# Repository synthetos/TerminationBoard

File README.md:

# TerminationBoard
Connector termination board for motorized winches

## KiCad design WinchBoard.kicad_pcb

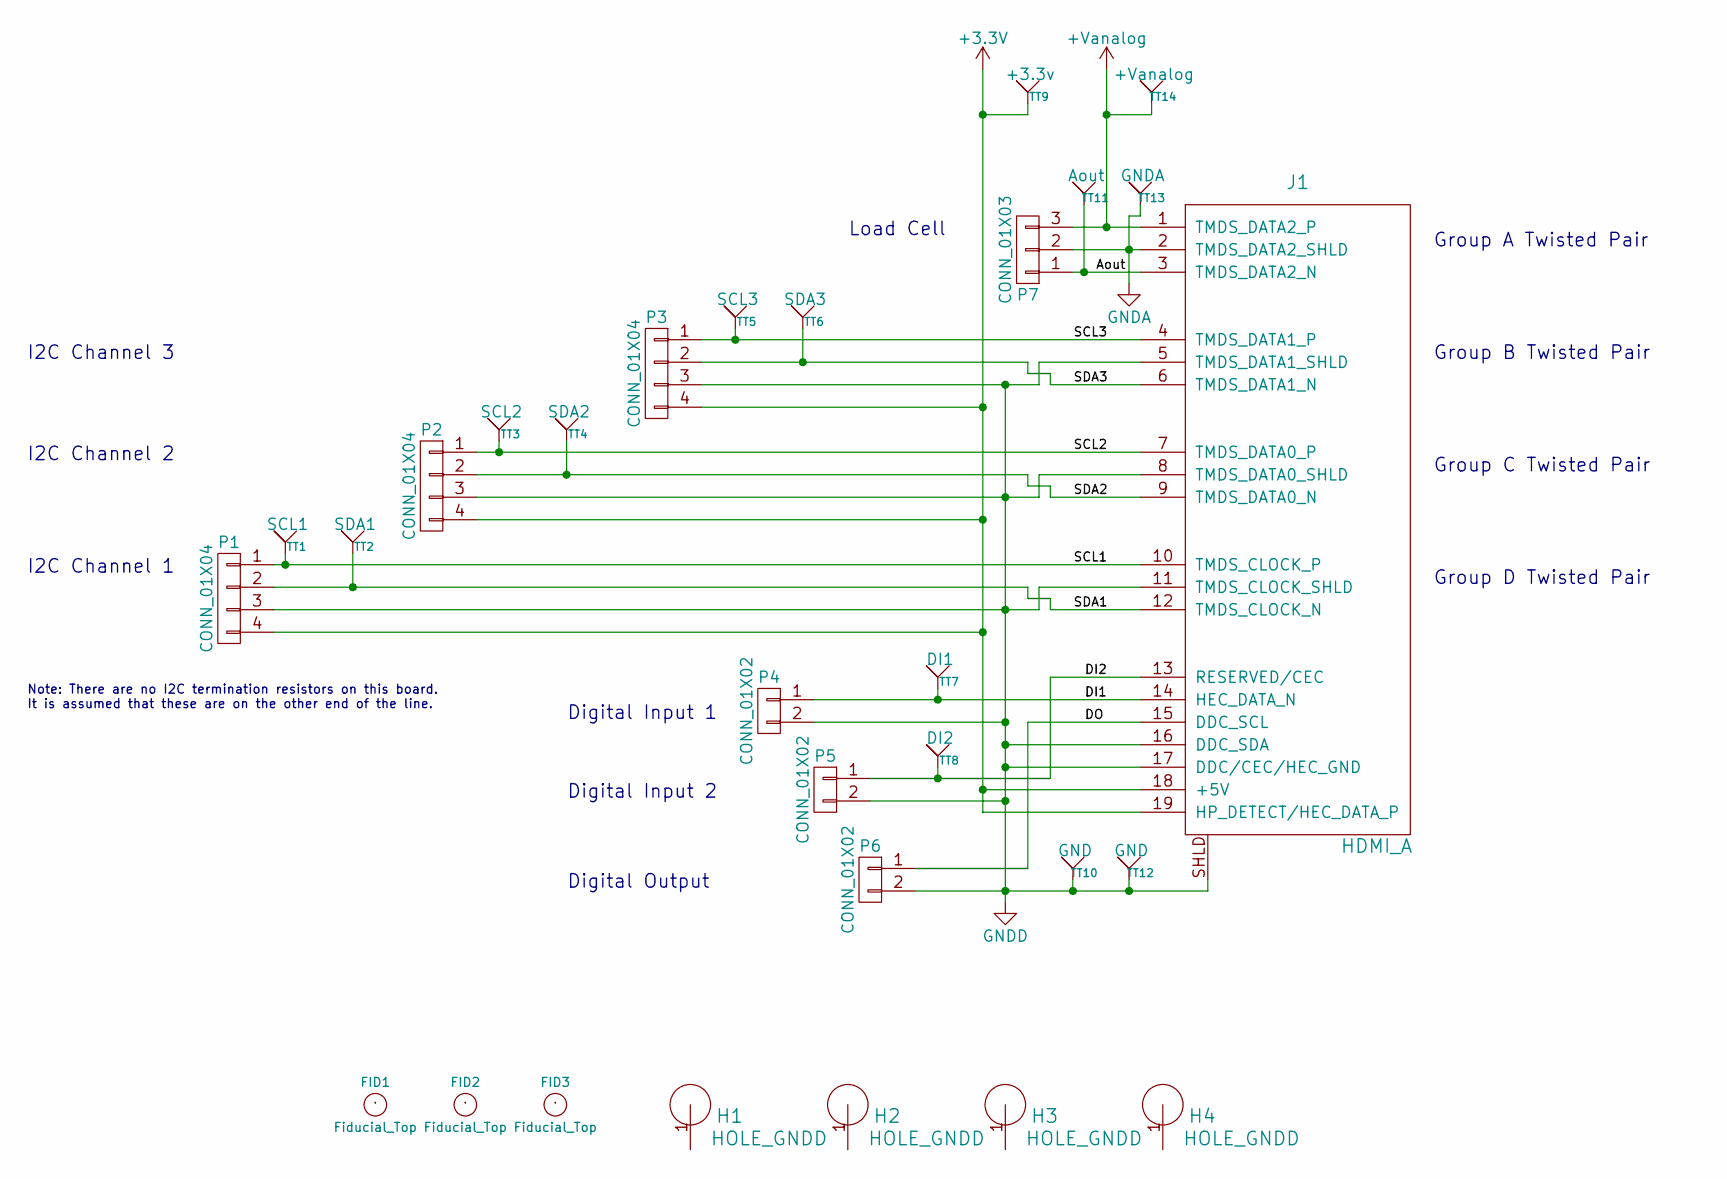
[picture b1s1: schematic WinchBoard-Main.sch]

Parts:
FID1, FID2, FID3: Fiducial_Top; Fiducial_0.040_Top
H1, H2, H3, H4: HOLE_GNDD; MountingHole_3.2mm_M3
J1: HDMI_A; FCI_10029449-11[13]RLF
P1, P2, P3: CONN_01X04; Molex_KK-6410-04_04x2.54mm_Straight
P4, P5, P6: CONN_01X02; Molex_KK-6410-02_02x2.54mm_Straight
P7: CONN_01X03; 0.100_1x3_small
TT1: SCL1; Test_Point_SMD_0.040_Bottom
TT2: SDA1; Test_Point_SMD_0.040_Bottom
TT3: SCL2; Test_Point_SMD_0.040_Bottom
TT4: SDA2; Test_Point_SMD_0.040_Bottom
TT5: SCL3; Test_Point_SMD_0.040_Bottom
TT6: SDA3; Test_Point_SMD_0.040_Bottom
TT7: DI1; Test_Point_SMD_0.040_Bottom
TT8: DI2; Test_Point_SMD_0.040_Bottom
TT9: +3.3v; Test_Point_SMD_0.040_Bottom
TT10, TT12: GND; Test_Point_SMD_0.040_Bottom
TT11: Aout; Test_Point_SMD_0.040_Bottom
TT13: GNDA; Test_Point_SMD_0.040_Bottom
TT14: +Vanalog; Test_Point_SMD_0.040_Bottom

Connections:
+3V3: J1.18 (+5V), J1.19 (HP_DETECT/HEC_DATA_P), P1.4, P2.4, P3.4, TT9.1
+Vanalog: J1.1 (TMDS_DATA2_P), P7.3, TT14.1
/Main/Aout: J1.3 (TMDS_DATA2_N), P7.1, TT11.1
/Main/DI1: J1.14 (HEC_DATA_N), P4.1, TT7.1
/Main/DI2: J1.13 (RESERVED/CEC), P5.1, TT8.1
/Main/DO: J1.15 (DDC_SCL), P6.1
/Main/SCL1: J1.10 (TMDS_CLOCK_P), P1.1, TT1.1
/Main/SCL2: J1.7 (TMDS_DATA0_P), P2.1, TT3.1
/Main/SCL3: J1.4 (TMDS_DATA1_P), P3.1, TT5.1
/Main/SDA1: J1.12 (TMDS_CLOCK_N), P1.2, TT2.1
/Main/SDA2: J1.9 (TMDS_DATA0_N), P2.2, TT4.1
/Main/SDA3: J1.6 (TMDS_DATA1_N), P3.2, TT6.1
GNDA: J1.2 (TMDS_DATA2_SHLD), P7.2, TT13.1
GNDD: J1.5 (TMDS_DATA1_SHLD), J1.8 (TMDS_DATA0_SHLD), J1.11 (TMDS_CLOCK_SHLD), J1.16 (DDC_SDA), J1.17 (DDC/CEC/HEC_GND), J1.SHLD, P1.3, P2.3, P3.3, P4.2, P5.2, P6.2, TT10.1, TT12.1

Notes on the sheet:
Note: There are no I2C termination resistors on this board. It is assumed that these are on the other end of the line.
Load Cell
I2C Channel 3
I2C Channel 2
I2C Channel 1
Digital Input 1
Digital Input 2
Digital Output
Group A Twisted Pair
Group B Twisted Pair
Group C Twisted Pair
Group D Twisted Pair

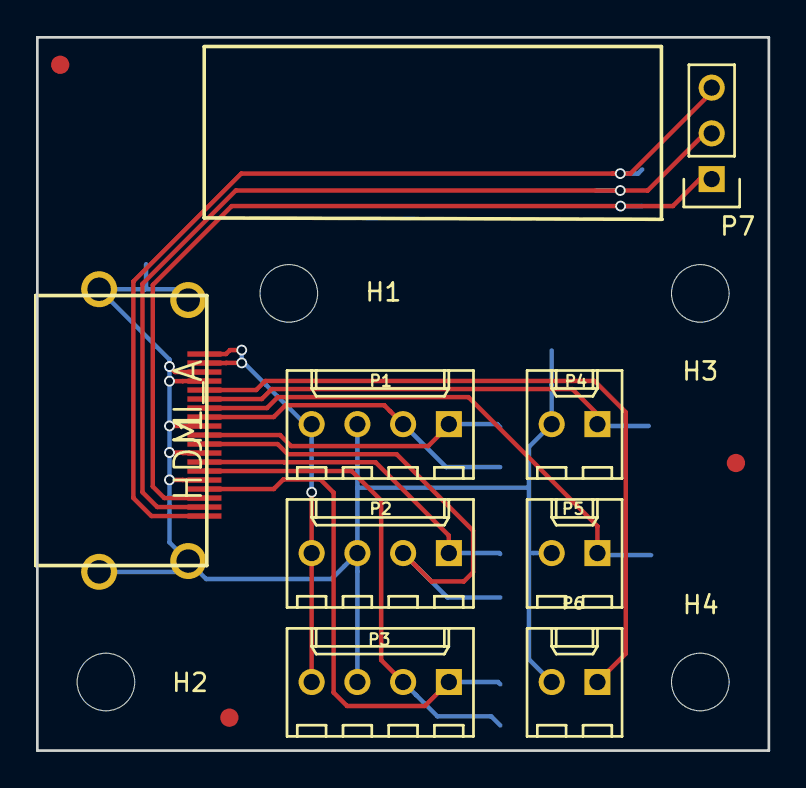
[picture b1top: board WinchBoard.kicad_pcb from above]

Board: 2 copper layers, 40.6 x 39.6 mm, 29 parts (0 on the bottom side), 14 nets.

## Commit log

2018-09-08 Added libraries
2018-09-08 Started schematic
2018-09-08 Checkpoint
2018-09-09 Added HDMI connector & libs, some component positioning, mounting holes, fiducials
2018-09-09 First complete schematic
2018-09-09 Checkpoint - component placement
2018-09-09 Version 001 - 1.4” x 1/6” locking connectors
2018-09-09 Double sided done for now.
2018-09-10 Semi-final commit before fab
2018-09-10 Submitted for fab
